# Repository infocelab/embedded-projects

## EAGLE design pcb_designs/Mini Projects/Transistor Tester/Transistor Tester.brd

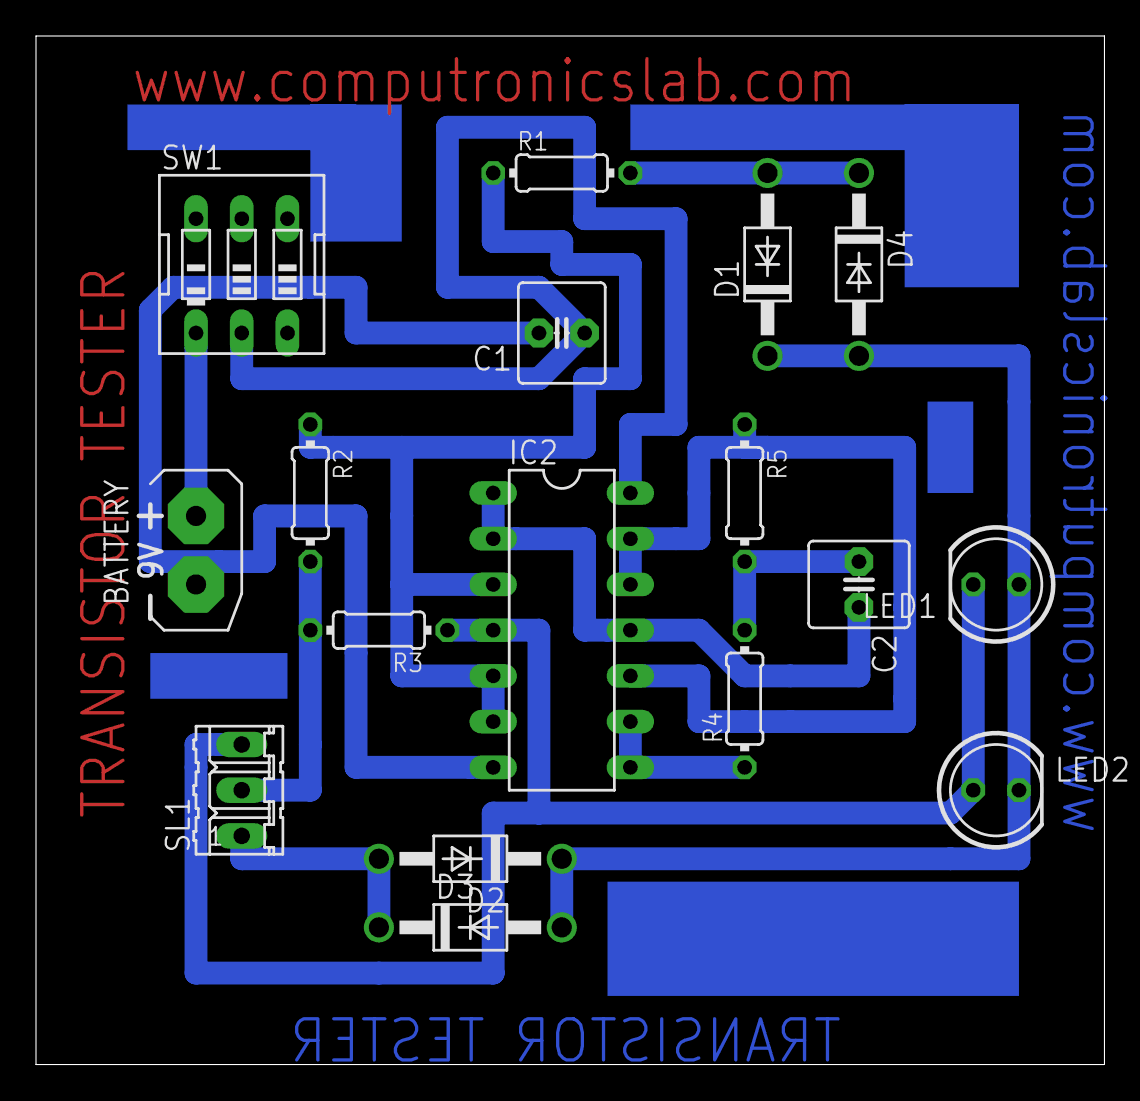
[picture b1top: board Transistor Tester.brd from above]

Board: 2 copper layers, 59.4 x 57.1 mm, 17 parts (0 on the bottom side), 13 nets.

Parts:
BATTERY: 9V; AB9V
C1: 100uf; C2.5-6
C2: 0.01uf; C2.5-6
D1, D2, D3, D4: 1N4007; DO41-10
IC2: CD4011; DIL14
LED1, LED2: 5mm; LED5MM
R1, R2: 220E; 0204/7
R3: 330E; 0204/7
R4, R5: 1M; 0204/7
SL1: 3 pin; 03P
SW1: on/off switch; EDG-03

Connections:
unnamed: C2.2, IC2.1, IC2.2, IC2.11
unnamed: IC2.3, IC2.5, IC2.6, R1.1, R2.1
unnamed: IC2.8, IC2.9, R4.1
unnamed: IC2.10, IC2.12, IC2.13, R5.1
unnamed: C2.1, R4.2, R5.2
unnamed: BATTERY.+, SW1.1
unnamed: C1.1, IC2.14, SW1.2
unnamed: BATTERY.-, C1.2, IC2.7
unnamed: D1.A, D4.C, R1.2
unnamed: R2.2, R3.2, SL1.2
unnamed: IC2.4, LED1.K, LED2.A, R3.1, SL1.3
unnamed: D1.C, D2.C, D3.A, D4.A, LED1.A, LED2.K
unnamed: D2.A, D3.C, SL1.1

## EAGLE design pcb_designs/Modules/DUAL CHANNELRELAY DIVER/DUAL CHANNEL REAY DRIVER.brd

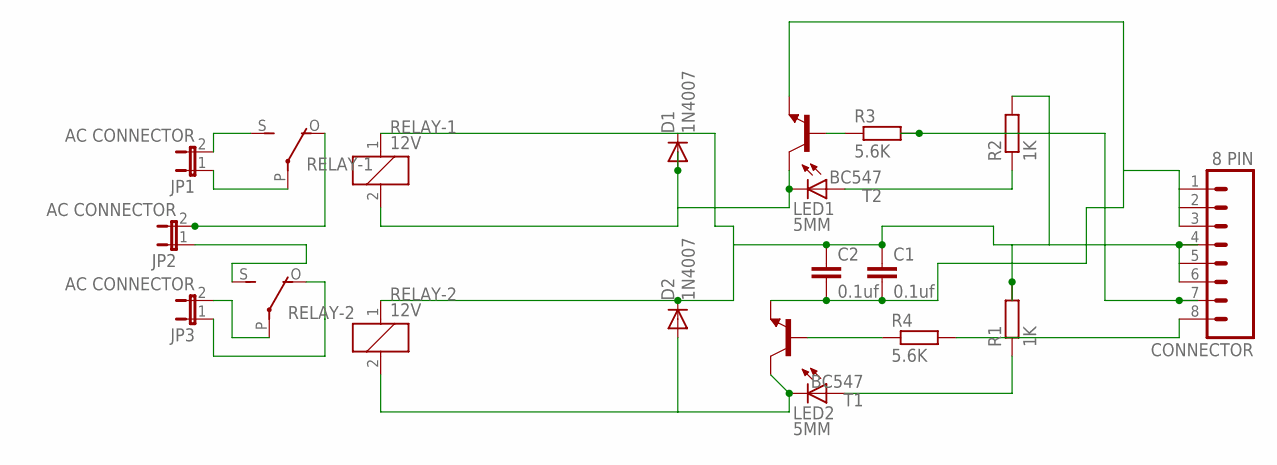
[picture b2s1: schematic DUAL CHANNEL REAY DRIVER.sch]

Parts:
C1, C2: 0.1uf; C2.5-3
CONNECTOR: 8 PIN; 08P
D1, D2: 1N4007; DO41-10
JP1, JP2, JP3: AC CONNECTOR; JP1
LED1, LED2: 5MM; LED5MM
R1, R2: 1K; 0204/7
R3, R4: 5.6K; 0204/7
RELAY-1, RELAY-2: 12V; G5LE
T1, T2: BC547; TO92

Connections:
unnamed: D1.A, LED1.K (C), RELAY-1.2, T2.3 (C)
unnamed: C1.1, C2.1, CONNECTOR.4, CONNECTOR.5, CONNECTOR.6, D1.C, D2.C, R1.2, R2.2, RELAY-1.1, RELAY-2.1
unnamed: R4.1, T1.2 (B)
unnamed: R3.1, T2.2 (B)
unnamed: LED1.A, R2.1
unnamed: LED2.A, R1.1
unnamed: JP1.2, RELAY-1.S
unnamed: JP1.1, RELAY-1.P
unnamed: JP2.2, RELAY-1.O
unnamed: JP2.1, RELAY-2.S
unnamed: JP3.2, RELAY-2.P
unnamed: JP3.1, RELAY-2.O
unnamed: C1.2, C2.2, CONNECTOR.1, CONNECTOR.2, CONNECTOR.3, T1.1 (E), T2.1 (E)
unnamed: CONNECTOR.7, R3.2
unnamed: CONNECTOR.8, R4.2
unnamed: D2.A, LED2.K (C), RELAY-2.2, T1.3 (C)

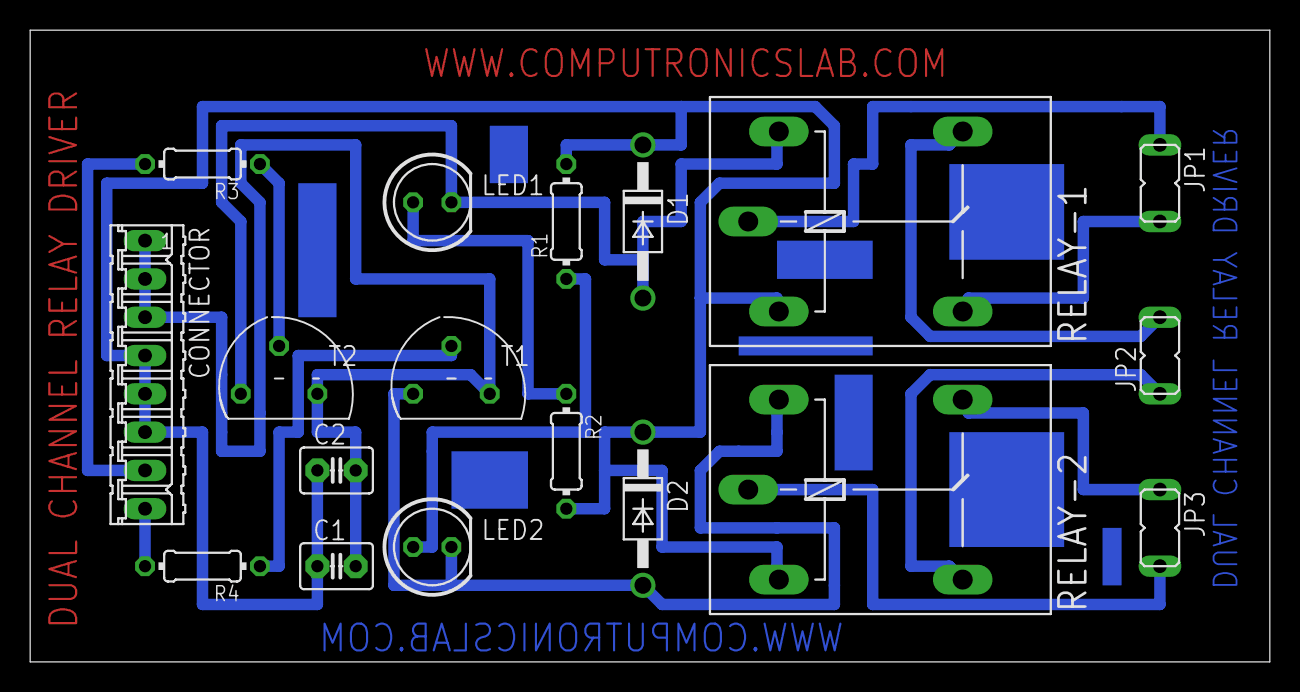
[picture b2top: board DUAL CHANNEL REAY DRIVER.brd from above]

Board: 2 copper layers, 82.2 x 41.9 mm, 18 parts (0 on the bottom side), 16 nets.

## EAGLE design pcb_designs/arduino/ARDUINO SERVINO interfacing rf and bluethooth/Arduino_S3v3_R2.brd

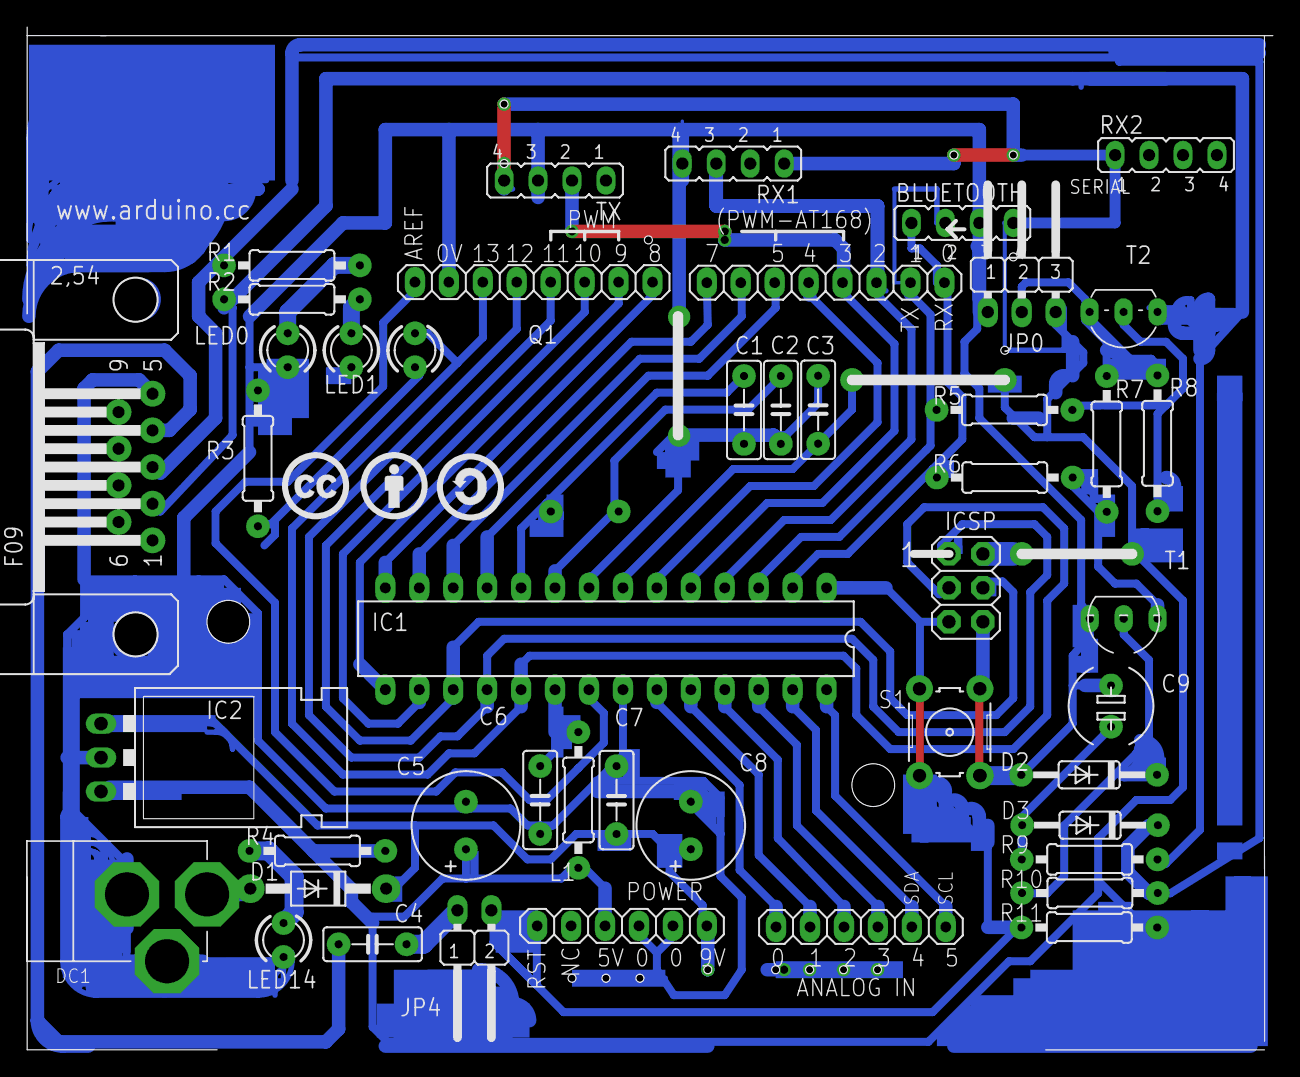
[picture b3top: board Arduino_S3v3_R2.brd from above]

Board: 2 copper layers, 93.2 x 76.5 mm, 50 parts (1 on the bottom side), 42 nets.

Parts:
BLUETOOTH: BLUETOOTH; JP4
C1, C2: 22p; C050-025X075
C3, C4, C6, C7: 100n; C050-025X075
C5, C8: 100u; E3,5-8
C9: 10u; E5-6
D1: 1N4004; DO41-10
D2, D3: 1N4148; DO35-10
DC1: DC21MMX; DC-21MM
IC1: ATMEGA8 (OR 168); DIL28-3
IC2: 78XXL
ICSP: ICSP; 2X03
J1: PORT D(D0-D7); 1X08
J2: PORT C(A0-A5); 1X06
J3: PORT B(D8-D13); 1X08
JP0: JP2W
JP4: AUTO RESET; JP1W
L1: 100uH; 0207/10
LED0: RX; LED3MM
LED1: TX; LED3MM
LED13: L; LED3MM
LED14: POWER LED; LED3MM
POWER: 1X06
Q1: 16000; Q
R1, R2: 1K; 0207/10
R3, R4, R6: 1k; 0207/10
R5, R7, R8, R10, R11: 10k; 0207/10
R9: 4k7; 0207/10
RX1, RX2: JP4
S1: B3F-10XX
T1: BC547; TO92
T2: BC557; TO92-EBC
TX: TX; JP4
U$1: CC
U$2: BY
U$3: SA
X1: F09H

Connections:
+5V: BLUETOOTH.4, C3.1, C5.+, IC1.7, IC2.OUT, ICSP.2, JP0.3, L1.2, POWER.3, R4.2, R11.2, RX1.1, RX2.1, TX.4
AREF: IC1.21, J3.8
GND: BLUETOOTH.3, C1.1, C2.1, C3.2, C5.-, C6.2, C7.1, C8.-, C9.+, D2.A, DC1.1, DC1.3, IC1.8, IC1.22, IC2.GND, ICSP.6, J3.7, JP0.1, LED0.K, LED1.K, LED14.K, POWER.4, POWER.5, R3.1, RX1.4, S1.1, S1.2, T1.1, TX.3, X1.5
M8RXD: BLUETOOTH.1, IC1.2, J1.1, R6.1
M8TXD: BLUETOOTH.2, IC1.3, J1.2, R5.1
unnamed: IC1.18, ICSP.1, J3.5
unnamed: C9.-, D3.A, R9.1
unnamed: LED14.A, R4.1
unnamed: IC1.17, ICSP.4, J3.4
unnamed: IC1.14, J3.1
unnamed: C1.2, IC1.9, Q1.1
unnamed: C2.2, IC1.10, Q1.2
unnamed: D1.A, DC1.2
unnamed: IC1.4, J1.3, RX1.3
unnamed: IC1.5, J1.4, TX.2
unnamed: IC1.6, J1.5
unnamed: IC1.11, J1.6
unnamed: IC1.12, J1.7
unnamed: IC1.13, J1.8
unnamed: IC1.23, J2.1
unnamed: IC1.24, J2.2
unnamed: IC1.25, J2.3
unnamed: IC1.26, J2.4
unnamed: IC1.27, J2.5
unnamed: IC1.28, J2.6
unnamed: IC1.15, J3.2
unnamed: IC1.16, J3.3
unnamed: D3.C, R1.2, R10.2, X1.3
unnamed: R6.2, R7.1, T1.3
unnamed: R5.2, R8.2, T2.B
unnamed: LED13.K, R3.2
unnamed: LED1.A, R2.1
unnamed: LED0.A, R1.1
unnamed: C4.1, JP4.2
unnamed: C4.2, X1.4
unnamed: R2.2, R9.2, T2.C, X1.2
unnamed: C6.1, IC1.20, L1.1
unnamed: D2.C, R10.1, T1.2
RESET: IC1.1, ICSP.5, JP4.1, POWER.1, R11.1, S1.3, S1.4
SCK: IC1.19, ICSP.3, J3.6, LED13.A
SERIAL_VCC: JP0.2, R7.2, R8.1, T2.E
VIN: C7.2, C8.+, D1.C, IC2.IN, POWER.6

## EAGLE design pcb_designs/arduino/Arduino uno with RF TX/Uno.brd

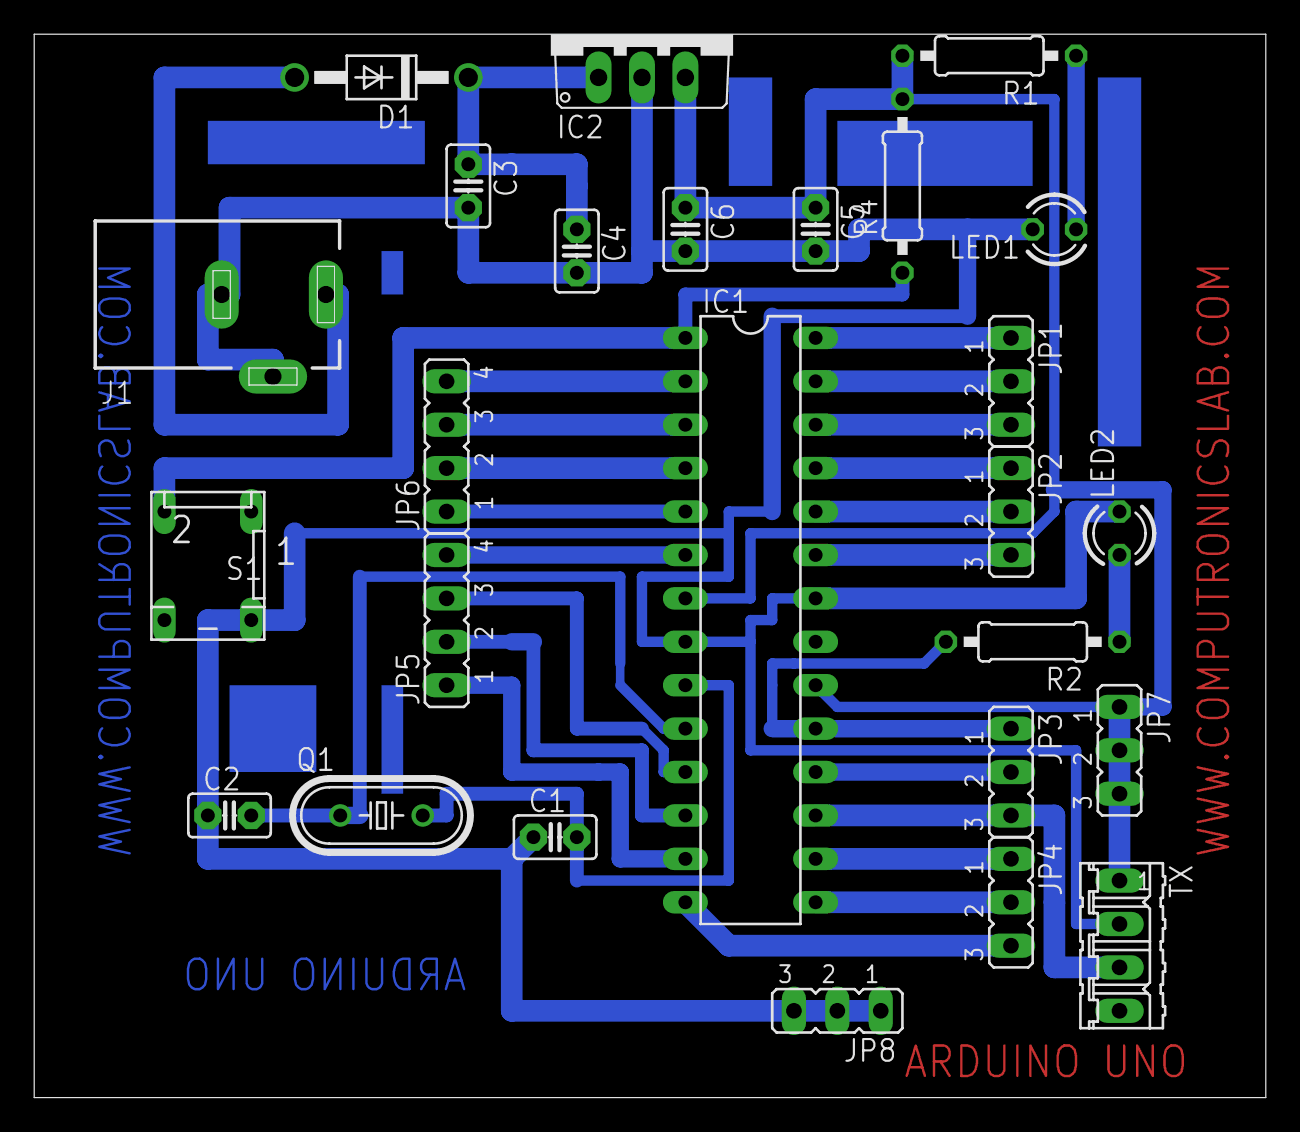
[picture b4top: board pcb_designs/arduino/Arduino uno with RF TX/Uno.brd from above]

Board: 2 copper layers, 72.1 x 62.2 mm, 26 parts (0 on the bottom side), 29 nets.

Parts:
C1, C2: 22pf; C2.5-2
C3: 470uF; C2.5-2
C4, C5: 0.1uf; C2.5-2
C6: 4.7uf; C2.5-2
D1: 1N4007; DO41-10
IC1: ATMEGA328; DIL28-3
IC2: 7805; TO220V
J1: DCJ0303
JP1, JP2, JP3, JP4: 3 pin; JP2
JP5, JP6: 4 pin; JP4
JP7, JP8: JP2
LED1, LED2: 3mm; LED3MM
Q1: 16MHZ; HC49/S
R1: 220R; 0207/10
R2: 330R; 0207/10
R4: 10K; 0207/10
S1: push switch; DP-02
TX: 04P

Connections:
unnamed: C1.2, IC1.9, Q1.2
unnamed: C2.2, IC1.10, Q1.1
unnamed: D1.A, J1.1
unnamed: C5.1, C6.1, IC1.7, IC1.20, IC2.3, JP7.1, JP7.2, JP7.3, R1.2, R4.2, TX.1
unnamed: C1.1, C2.1, C3.2, C4.2, C5.2, C6.2, IC1.8, IC1.22, IC2.2, J1.2, J1.3, JP8.1, JP8.2, JP8.3, LED1.K, LED2.K, S1.4, TX.2
unnamed: LED1.A, R1.1
unnamed: C3.1, C4.1, D1.C, IC2.1
unnamed: IC1.28, JP1.1
unnamed: IC1.27, JP1.2
unnamed: IC1.26, JP1.3
unnamed: IC1.25, JP2.1
unnamed: IC1.24, JP2.2
unnamed: IC1.23, JP2.3
unnamed: IC1.5, JP6.1
unnamed: IC1.2, JP6.4
unnamed: IC1.3, JP6.3
unnamed: IC1.4, JP6.2
unnamed: IC1.6, JP5.4
unnamed: IC1.12, JP5.2
unnamed: IC1.11, JP5.3
unnamed: IC1.14, JP4.3
unnamed: IC1.15, JP4.2
unnamed: IC1.16, JP4.1
unnamed: IC1.17, JP3.3, TX.3
unnamed: IC1.18, JP3.2
unnamed: IC1.19, JP3.1, R2.2
unnamed: IC1.13, JP5.1
unnamed: IC1.1, R4.1, S1.2
unnamed: LED2.A, R2.1

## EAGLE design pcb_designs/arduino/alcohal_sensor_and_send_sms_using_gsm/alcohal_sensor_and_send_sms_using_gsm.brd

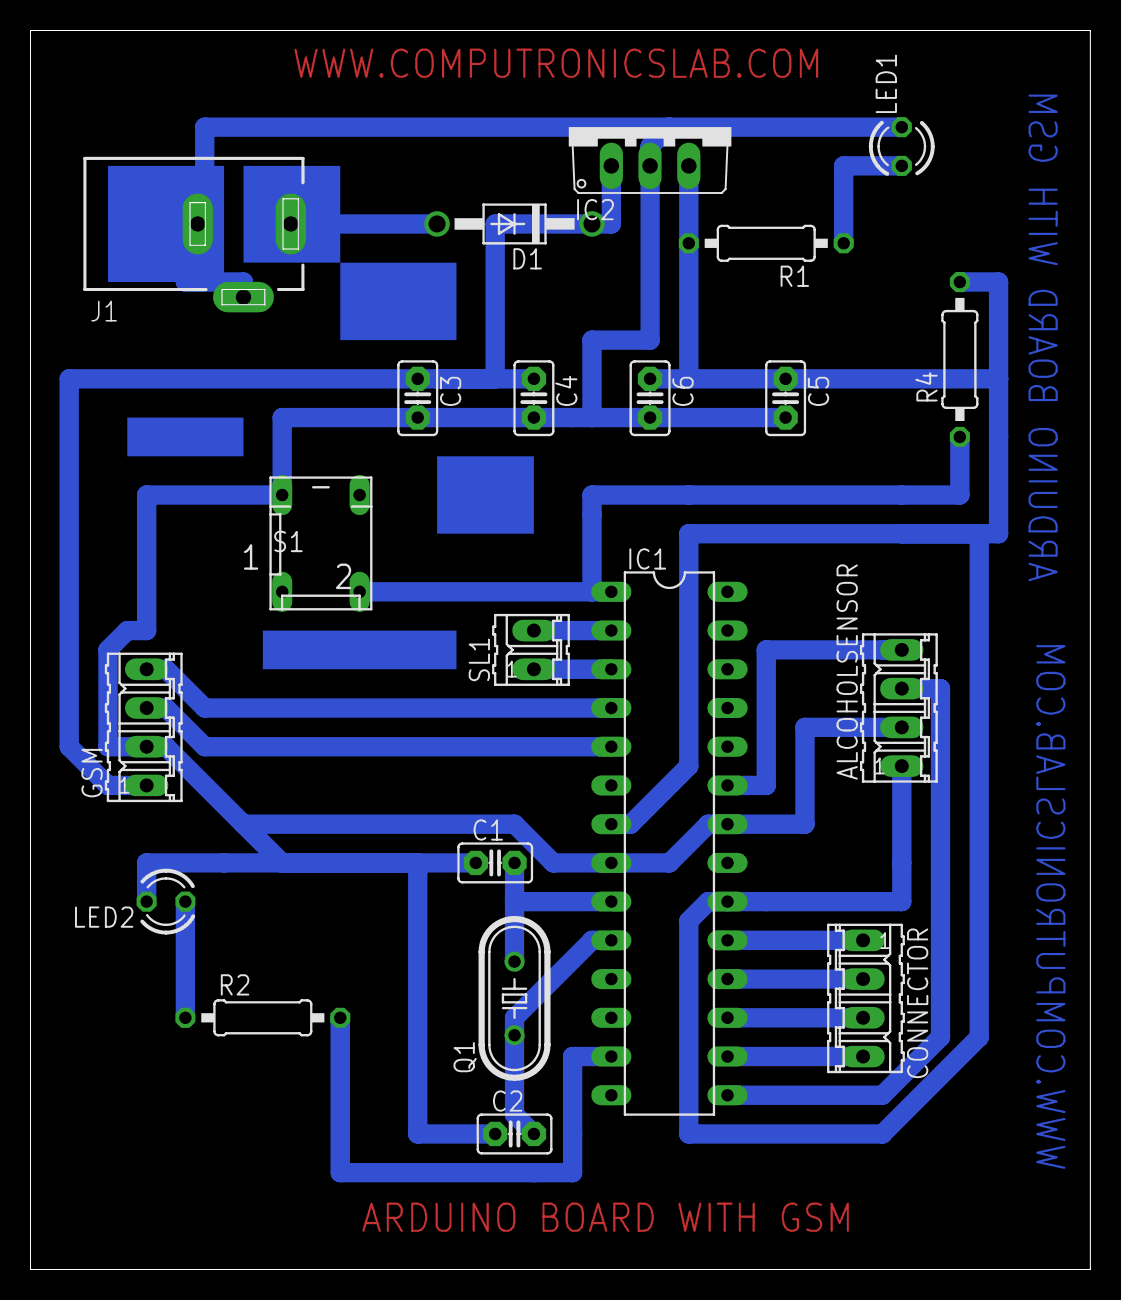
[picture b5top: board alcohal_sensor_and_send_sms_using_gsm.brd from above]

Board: 2 copper layers, 69.5 x 81.3 mm, 21 parts (0 on the bottom side), 20 nets.

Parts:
ALCOHOLSENSOR: 04P
C1, C2: 22pf; C2.5-2
C3: 100UF; C2.5-2
C4, C5: 0.1uf; C2.5-2
C6: 4.7uf; C2.5-2
CONNECTOR: 4 pin; 04P
D1: 1N4007; DO41-10
GSM: 04P
IC1: ATMEGA328; DIL28-3
IC2: 7805; TO220V
J1: DCJ0303
LED1, LED2: LED3MM
Q1: 16MHZ; HC49/S
R1: 220R; 0207/10
R2: 330R; 0207/10
R4: 10K; 0207/10
S1: DP-02
SL1: 2 pin; 02P

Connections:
unnamed: C1.2, IC1.9, Q1.2
unnamed: C2.2, IC1.10, Q1.1
unnamed: D1.A, J1.1
unnamed: ALCOHOLSENSOR.1, C5.1, C6.1, IC1.7, IC1.20, IC2.3, R1.2, R4.2
unnamed: ALCOHOLSENSOR.2, C1.1, C2.1, C3.2, C4.2, C5.2, C6.2, GSM.2, IC1.8, IC1.22, IC2.2, J1.2, J1.3, LED1.K, LED2.K, S1.4
unnamed: LED1.A, R1.1
unnamed: C3.1, C4.1, D1.C, GSM.1, IC2.1
unnamed: GSM.4, IC1.4
unnamed: GSM.3, IC1.5
unnamed: IC1.3, SL1.1
unnamed: IC1.2, SL1.2
unnamed: ALCOHOLSENSOR.3, IC1.15
unnamed: ALCOHOLSENSOR.4, IC1.23
unnamed: CONNECTOR.1, IC1.19
unnamed: CONNECTOR.2, IC1.18
unnamed: CONNECTOR.3, IC1.17
unnamed: CONNECTOR.4, IC1.16
unnamed: IC1.13, R2.2
unnamed: IC1.1, R4.1, S1.2
unnamed: LED2.A, R2.1

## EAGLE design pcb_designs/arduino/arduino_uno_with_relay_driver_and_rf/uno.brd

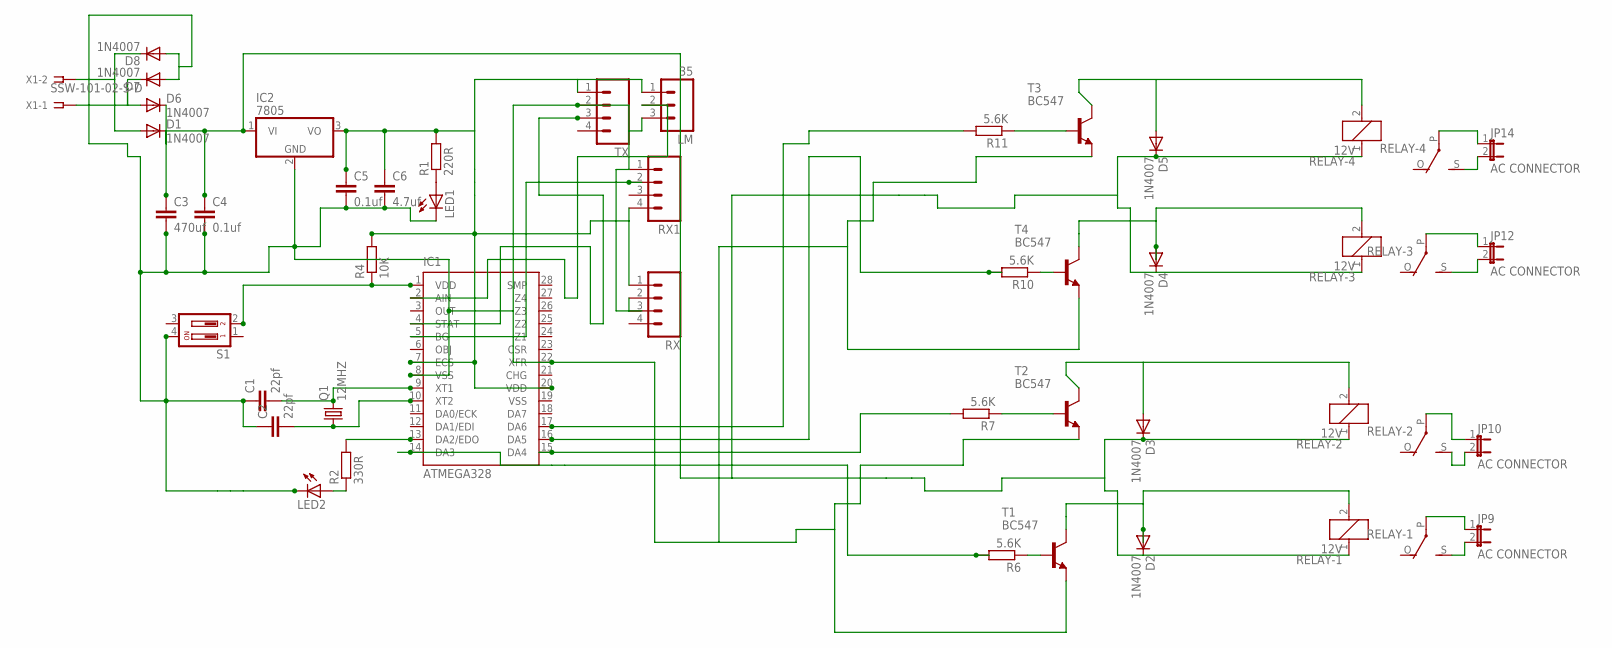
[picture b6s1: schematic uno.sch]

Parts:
C1, C2: 22pf; C2.5-2
C3: 470uf; C2.5-2
C4, C5: 0.1uf; C2.5-2
C6: 4.7uf; C2.5-2
D1, D2, D3, D4, D5, D6, D7, D8: 1N4007; DO41-10
IC1: ATMEGA328; DIL28-3
IC2: 7805; TO220V
JP9, JP10, JP12, JP14: AC CONNECTOR; JP1
LED1, LED2: LED3MM
LM: 35; 03P
Q1: 12MHZ; HC49/S
R1: 220R; 0207/10
R2: 330R; 0207/10
R4: 10K; 0207/10
R6, R7, R10, R11: 5.6K; 0204/7
RELAY-1, RELAY-2, RELAY-3, RELAY-4: 12V; G5LE
RX, RX1: M04; 04P
S1: DP02; DP-02
T1, T2, T3, T4: BC547; TO92
TX: M04; 04P
X1: SSW-101-02-S-D

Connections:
unnamed: C1.2, IC1.9 (XT1), Q1.2
unnamed: C2.2, IC1.10 (XT2), Q1.1
unnamed: C5.1, C6.1, IC1.7 (ECS), IC1.20 (VDD), IC2.3 (VO), LM.1, R1.2, R4.2, RX.1, RX1.4, TX.1
unnamed: LED1.A, R1.1
unnamed: C3.1, C4.1, D1.C, D2.C, D3.C, D4.C, D5.C, D6.C, IC2.1 (VI), RELAY-1.1, RELAY-2.1, RELAY-3.1, RELAY-4.1
unnamed: IC1.2 (AIN), LM.2
unnamed: IC1.5 (BG), RX1.2
unnamed: D6.A, D7.C, X1.1
unnamed: IC1.4 (STAT), TX.3
unnamed: D1.A, D8.C, X1.2
unnamed: IC1.13 (DA2/EDO), R2.2
unnamed: D2.A, RELAY-1.2, T1.3 (C)
unnamed: R7.1, T2.2 (B)
unnamed: R6.1, T1.2 (B)
unnamed: IC1.1 (VDD), R4.1, S1.2
unnamed: LED2.A, R2.1
unnamed: JP9.2, RELAY-1.S
unnamed: JP9.1, RELAY-1.P
unnamed: JP10.2, RELAY-2.S
unnamed: JP10.1, RELAY-2.P
unnamed: IC1.14 (DA3), R6.2
unnamed: D3.A, RELAY-2.2, T2.3 (C)
unnamed: D4.A, RELAY-3.2, T4.3 (C)
unnamed: R11.1, T3.2 (B)
unnamed: R10.1, T4.2 (B)
unnamed: JP12.2, RELAY-3.S
unnamed: JP12.1, RELAY-3.P
unnamed: JP14.2, RELAY-4.S
unnamed: JP14.1, RELAY-4.P
unnamed: C1.1, C2.1, C3.2, C4.2, C5.2, C6.2, D7.A, D8.A, IC1.8 (VSS), IC1.22 (XFR), IC2.2 (GND), LED1.K (C), LED2.K (C), LM.3, RX.2, RX1.1, S1.4, T1.1 (E), T2.1 (E), T3.1 (E), T4.1 (E), TX.2
unnamed: IC1.16 (DA5), R10.2
unnamed: IC1.17 (DA6), R11.2
unnamed: D5.A, RELAY-4.2, T3.3 (C)
unnamed: IC1.15 (DA4), R7.2

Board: 2 copper layers, 44 parts (0 on the bottom side), 34 nets, no tracks yet.

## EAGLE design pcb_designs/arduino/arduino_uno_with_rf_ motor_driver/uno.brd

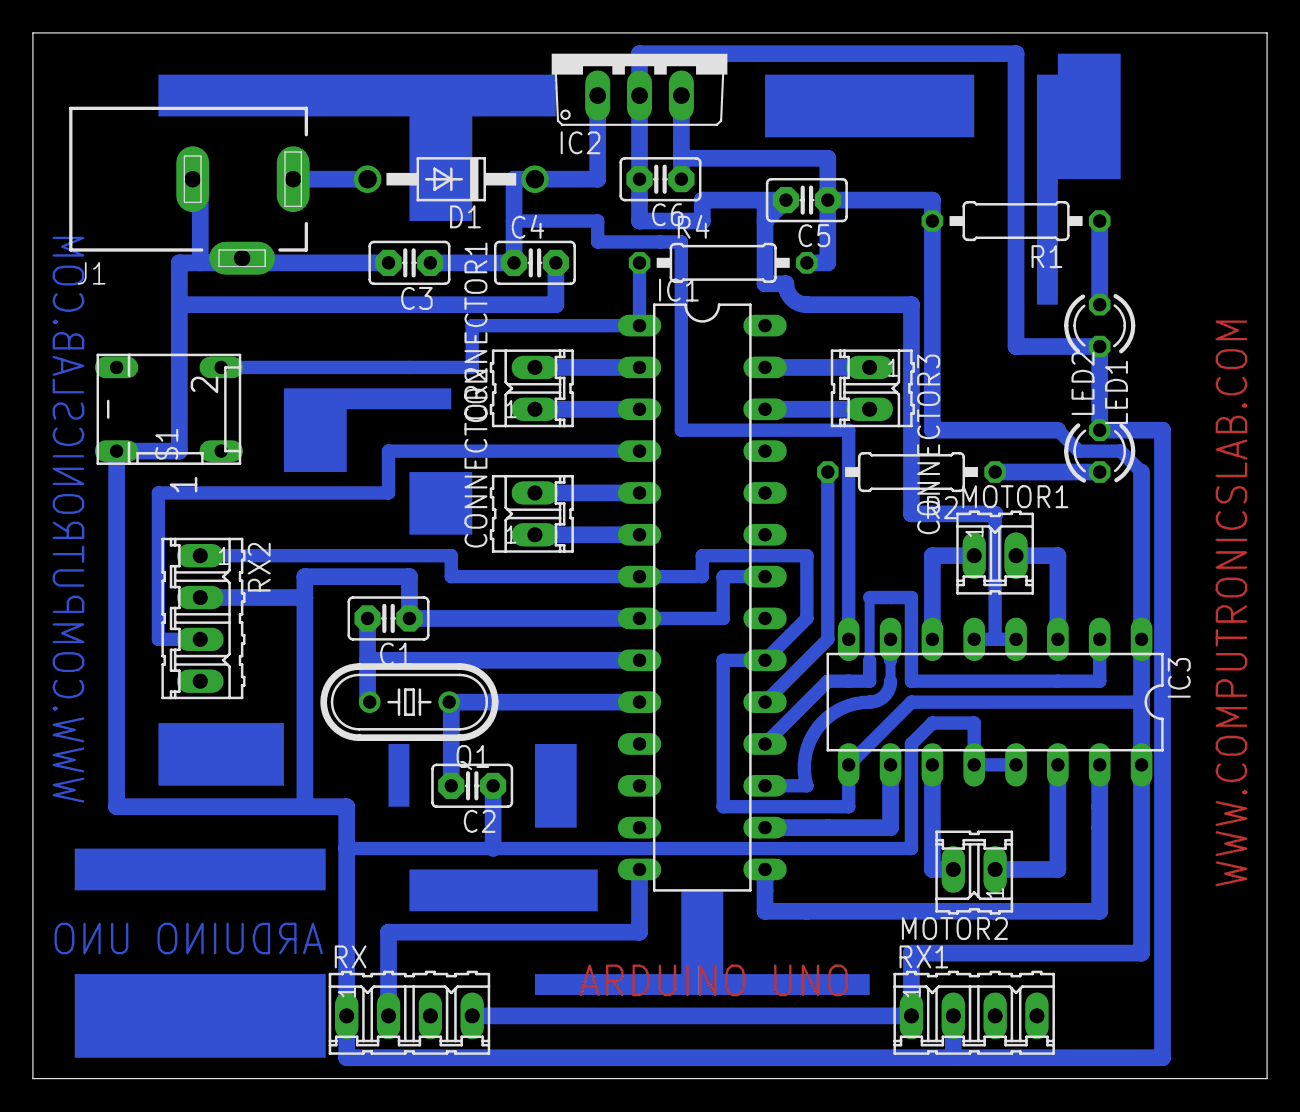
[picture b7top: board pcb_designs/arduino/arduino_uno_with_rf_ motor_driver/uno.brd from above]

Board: 2 copper layers, 74.9 x 63.5 mm, 26 parts (0 on the bottom side), 26 nets.

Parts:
C1, C2: 22pf; C2.5-2
C3: 470uF; C2.5-2
C4, C5: 0.1uf; C2.5-2
C6: 4.7uf; C2.5-2
CONNECTOR1, CONNECTOR2: 2 pin; 02P
CONNECTOR3: 02P
D1: 1N4007; DO41-10
IC1: ATMEGA328; DIL28-3
IC2: 7805; TO220V
IC3: L293D; DIL16
J1: DCJ0303
LED1, LED2: 3mm; LED3MM
MOTOR1, MOTOR2: 02P
Q1: 16MHZ; HC49/S
R1: 220R; 0207/10
R2: 330R; 0207/10
R4: 10K; 0207/10
RX, RX1, RX2: 04P
S1: push switch; DP-02

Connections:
unnamed: C1.2, IC1.9, Q1.2
unnamed: C2.2, IC1.10, Q1.1
unnamed: D1.A, J1.1
unnamed: C3.1, C4.1, D1.C, IC2.1, IC3.8
unnamed: C1.1, C2.1, C3.2, C4.2, C5.2, C6.2, IC1.8, IC1.22, IC2.2, IC3.4, IC3.5, IC3.12, IC3.13, J1.2, J1.3, LED1.K, LED2.K, RX.1, RX1.2, RX2.2, S1.4
unnamed: LED1.A, R1.1
unnamed: IC1.17, IC3.7
unnamed: CONNECTOR1.1, IC1.3
unnamed: CONNECTOR1.2, IC1.2
unnamed: CONNECTOR2.1, IC1.6
unnamed: CONNECTOR2.2, IC1.5
unnamed: CONNECTOR3.1, IC1.27
unnamed: CONNECTOR3.2, IC1.26
unnamed: IC1.14, RX.2
unnamed: IC1.18, IC3.2
unnamed: IC1.15, IC3.15
unnamed: IC1.4, RX2.3
unnamed: IC1.16, IC3.10
unnamed: IC3.14, MOTOR2.1
unnamed: IC1.19, R2.2
unnamed: IC3.11, MOTOR2.2
unnamed: IC1.1, R4.1, S1.2
unnamed: LED2.A, R2.1
unnamed: C5.1, C6.1, IC1.7, IC1.20, IC2.3, IC3.1, IC3.9, IC3.16, R1.2, R4.2, RX.4, RX1.1, RX2.1
unnamed: IC3.6, MOTOR1.1
unnamed: IC3.3, MOTOR1.2

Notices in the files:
pcb_designs/arduino/ARDUINO SERVINO interfacing rf and bluethooth/Arduino_S3v3_R2.brd:
Released under the Creative Commons Attribution Share-Alike 2.5 License
http://creativecommons.org/licenses/by-sa/2.5
CC BY SA 2.5
